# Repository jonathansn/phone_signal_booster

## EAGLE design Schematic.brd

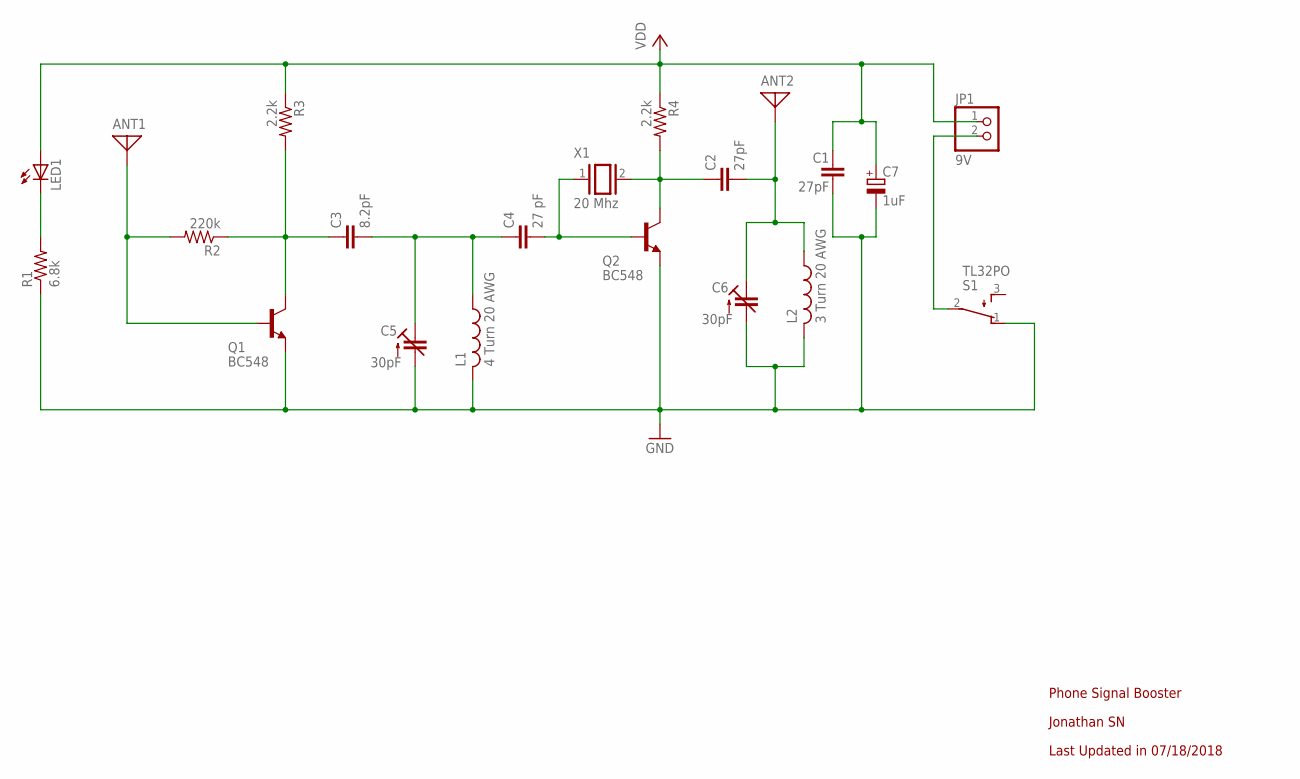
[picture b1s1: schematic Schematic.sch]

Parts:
ANT1, ANT2: ANTENNA; PAD-01
C1, C2: 27pF; C2.5-3
C3: 8.2pF; C2.5-3
C4: 27 pF; C2.5-3
C5, C6: 30pF; CTRIM808-BC
C7: 1uF; E2-5
JP1: 9V; 1X02
L1: 4 Turn 20 AWG; 0204/5
L2: 3 Turn 20 AWG; 0204/5
LED1: LED3MM
Q1, Q2: BC548; TO92-EBC
R1: 6.8k; 0207/7
R2: 220k; 0207/7
R3, R4: 2.2k; 0207/7
S1: TL32PO; TL3XPO
X1: 20 Mhz; QS

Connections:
ANT1: ANT1.1, Q1.B, R2.2
ANT2: ANT2.1, C2.2, C6.1 (E), L2.1
BAT-: JP1.2, S1.2
CRYSTAL1: C4.2, Q2.B, X1.1
CRYSTAL2: C2.1, Q2.C, R4.2, X1.2
GND: C1.2, C5.2 (A), C6.2 (A), C7.-, L1.2, L2.2, Q1.E, Q2.E, R1.1, S1.1 (O)
L4TURN: C3.2, C4.1, C5.1 (E), L1.1
LED-: LED1.K (C), R1.2
unnamed: C3.1, Q1.C, R2.1, R3.2
VDD: C1.1, C7.+, JP1.1, LED1.A, R3.1, R4.1

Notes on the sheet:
Phone Signal Booster
Jonathan SN
Last Updated in 07/18/2018

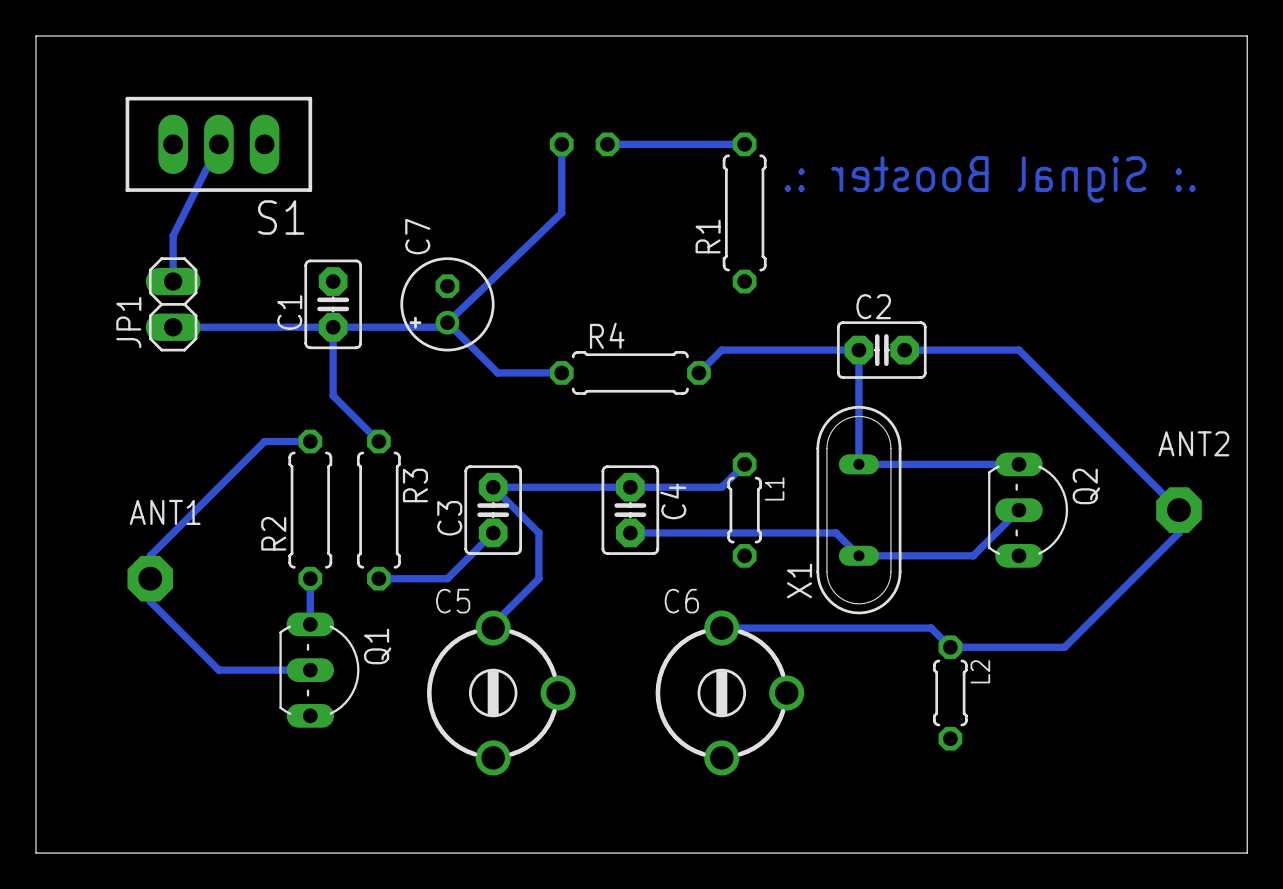
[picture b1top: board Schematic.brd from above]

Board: 2 copper layers, 67.3 x 45.4 mm, 21 parts (1 on the bottom side), 10 nets.

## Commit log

2018-07-18 Schematic File
2018-07-18 Add PCB and more modifications
2018-07-18 Add Docs
